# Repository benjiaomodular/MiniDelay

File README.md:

# MiniDelay

A three-knob delay module based on Rene Schmitz' PT2399 delay design. It’s a simple setup with input and output sections designed to work with Eurorack modular synthesizer levels (10Vpp).

# More info
For more information about this project, check out my website: https://benjiaomodular.com/post/2022-09-11-mini-delay/

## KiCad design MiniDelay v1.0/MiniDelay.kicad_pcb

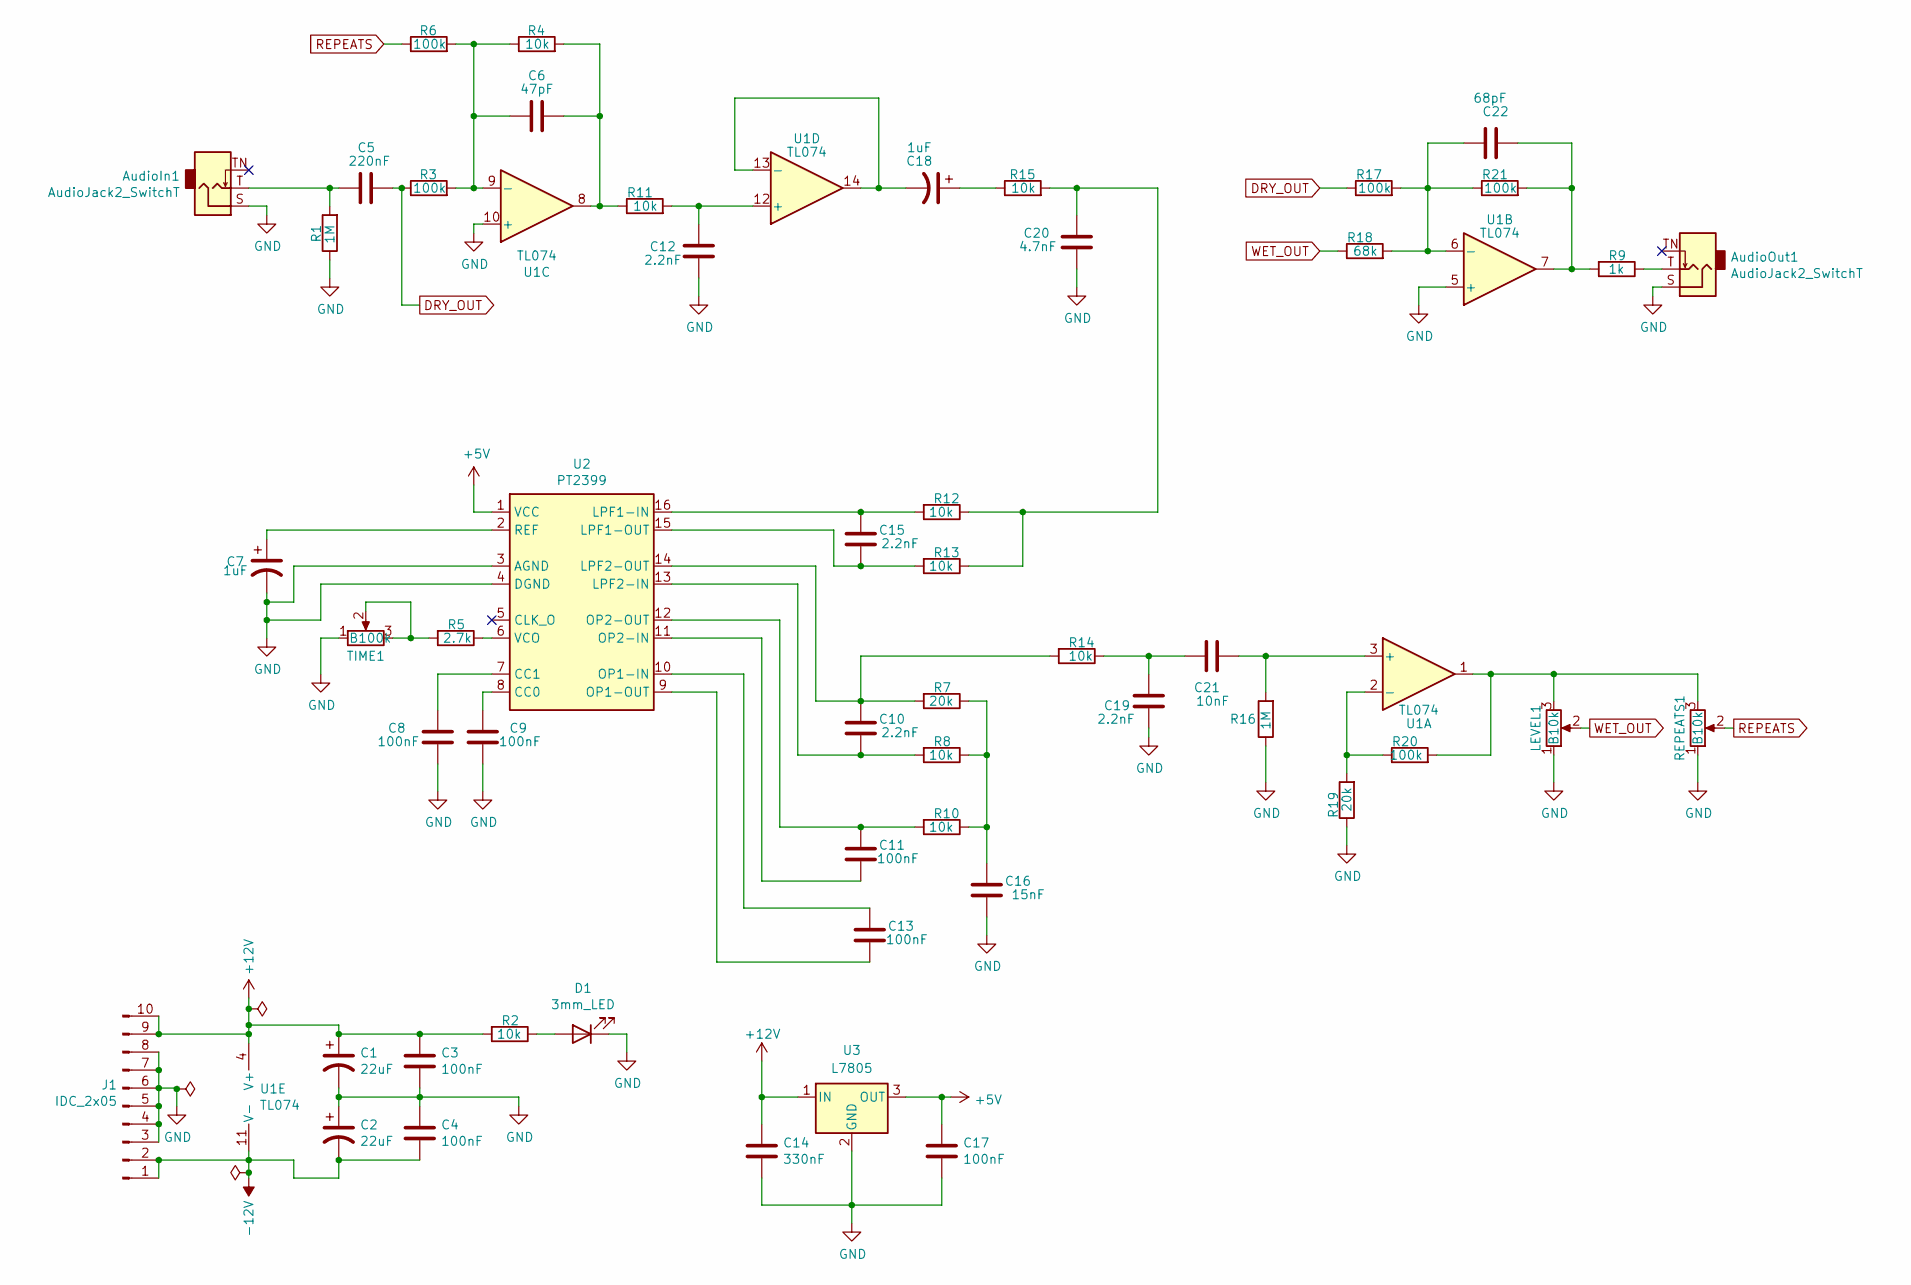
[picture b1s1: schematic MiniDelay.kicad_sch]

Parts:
AudioIn1: AudioJack2_SwitchT; AudioJack_3.5mm; Manufacturers Part Numb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 PJ-3001F
AudioOut1: AudioJack2_SwitchT; AudioJack_3.5mm; Manufacturers Part Numb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 PJ-3001F
C1, C2: 22uF; C_0805_2012Metric_Pad1.18x1.45mm_HandSolder; Mfg # CC0805KRX7R9BB104; LCSC Part # C49678
C3, C4, C8, C9, C11, C13, C17: 100nF; C_0603_1608Metric_Pad1.08x0.95mm_HandSolder; Mfg # CC0603JRX7R9BB104; LCSC Part # C91183
C5: 220nF; C_0603_1608Metric_Pad1.08x0.95mm_HandSolder; Mfg # GCM188R71H224KA64D; LCSC Part # C97857
C6: 47pF; C_0603_1608Metric_Pad1.08x0.95mm_HandSolder; Mfg # CC0603JRNPO9BN470; LCSC Part # C105622
C7, C18: 1uF; C_0603_1608Metric_Pad1.08x0.95mm_HandSolder; Mfg # UMK107AB7105KA-T; LCSC Part # C105174
C10, C12, C15, C19: 2.2nF; C_0603_1608Metric_Pad1.08x0.95mm_HandSolder; Mfg # CC0603JRNPO9BN222; LCSC Part # C107043
C14: 330nF; C_0603_1608Metric_Pad1.08x0.95mm_HandSolder; Mfg # CC0603KRX7R8BB334; LCSC Part # C107070
C16: 15nF; C_0603_1608Metric_Pad1.08x0.95mm_HandSolder; Mfg # AC0603KRX7R0BB153; LCSC Part # C2210963
C20: 4.7nF; C_0603_1608Metric_Pad1.08x0.95mm_HandSolder; Mfg # CC0603JRX7R9BB472; LCSC Part # C115060
C21: 10nF; C_0603_1608Metric_Pad1.08x0.95mm_HandSolder; Mfg # CC0603JRX7R9BB103; LCSC Part # C115056
C22: 68pF; C_0603_1608Metric_Pad1.08x0.95mm_HandSolder; Mfg # CC0603GRNPO9BN680; LCSC Part # C519457
D1: 3mm_LED; LED_D3.0mm; Manufacturers Part Numb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 EL304RD; LCSC Part # C2856645
J1: IDC_2x05; IDC-Header_2x05_P2.54mm_Vertical; Manufacturers Part Numb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 X9555WV-2X05-6TV01; LCSC Part # C706914
LEVEL1: B10k; Potentiometer_RV09; Manufacturers Part Numb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 RD901F-40-15R1-B10K
R1, R16: 1M; R_0603_1608Metric_Pad0.98x0.95mm_HandSolder; Mfg # RC0603FR-071ML; LCSC Part # C105578
R2, R4, R8, R10, R11, R12, R13, R14, R15: 10k; R_0603_1608Metric_Pad0.98x0.95mm_HandSolder; Mfg # AC0603FR-0710KL; LCSC Part # C116677
R3, R6, R17, R20, R21: 100k; R_0603_1608Metric_Pad0.98x0.95mm_HandSolder; Mfg # RC0603FR-07100KL; LCSC Part # C14675
R5: 2.7k; R_0603_1608Metric_Pad0.98x0.95mm_HandSolder; Mfg # RC0603FR-072K7L; LCSC Part # C114612
R7, R19: 20k; R_0603_1608Metric_Pad0.98x0.95mm_HandSolder; Mfg # RC0603FR-0720KL; LCSC Part # C105575
R9: 1k; R_0603_1608Metric_Pad0.98x0.95mm_HandSolder; Mfg # RC0603FR-071KL; LCSC Part # C22548
R18: 68k; R_0603_1608Metric_Pad0.98x0.95mm_HandSolder; Mfg # RC0603FR-0768KL; LCSC Part # C114633
REPEATS1: B10k; Potentiometer_RV09; Manufacturers Part Numb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 RD901F-40-15R1-B10K
TIME1: B100k; Potentiometer_RV09; Manufacturers Part Numb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 RD901F-40-15R1-B100K
U1: TL074; SOIC-14_3.9x8.7mm_P1.27mm; Mfg # TL074IDT; LCSC Part # C107644
U2: PT2399; SOP-16_4.55x10.3mm_P1.27mm; Mfg # PT2399-SN; LCSC Part # C126407
U3: L7805; TO-252-2; Mfg # L7805CDT-TR; LCSC Part # C310413

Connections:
+5V: C17.1, U2.1 (VCC), U3.3 (OUT)
+12V: C1.1, C3.1, C14.1, J1.9, J1.10, R2.2, U1.4 (V+), U3.1 (IN)
-12V: C2.2, C4.2, J1.1, J1.2, U1.11 (V-)
DRY_OUT: C5.1, R3.1, R17.1
GND: AudioIn1.S, AudioOut1.S, C1.2, C2.1, C3.2, C4.1, C7.2, C8.1, C9.1, C12.1, C14.2, C16.1, C17.2, C19.1, C20.2, D1.1 (K), J1.3, J1.4, J1.5, J1.6, J1.7, J1.8, LEVEL1.1, R1.1, R16.1, R19.1, REPEATS1.1, TIME1.1, U1.5 (+), U1.10 (+), U2.3 (AGND), U2.4 (DGND), U3.2 (GND)
unnamed: AudioIn1.T, C5.2, R1.2
unnamed: AudioOut1.T, R9.1
unnamed: C6.1, R4.2, R11.1, U1.8
unnamed: C6.2, R3.2, R4.1, R6.2, U1.9 (-)
unnamed: C7.1, U2.2 (REF)
unnamed: C8.2, U2.7 (CC1)
unnamed: C9.2, U2.8 (CC0)
unnamed: C10.1, R8.2, U2.13 (LPF2-IN)
unnamed: C10.2, R7.2, R14.2, U2.14 (LPF2-OUT)
unnamed: C11.1, U2.11 (OP2-IN)
unnamed: C11.2, R10.2, U2.12 (OP2-OUT)
unnamed: C12.2, R11.2, U1.12 (+)
unnamed: C13.1, U2.9 (OP1-OUT)
unnamed: C13.2, U2.10 (OP1-IN)
unnamed: C15.1, R13.2, U2.15 (LPF1-OUT)
unnamed: C15.2, R12.2, U2.16 (LPF1-IN)
unnamed: C16.2, R7.1, R8.1, R10.1
unnamed: C18.1, R15.1
unnamed: C18.2, U1.13 (-), U1.14
unnamed: C19.2, C21.1, R14.1
unnamed: C20.1, R12.1, R13.1, R15.2
unnamed: C21.2, R16.2, U1.3 (+)
unnamed: C22.1, R9.2, R21.2, U1.7
unnamed: C22.2, R17.2, R18.2, R21.1, U1.6 (-)
unnamed: D1.2 (A), R2.1
unnamed: LEVEL1.3, R20.2, REPEATS1.3, U1.1
unnamed: R5.1, U2.6 (VCO)
unnamed: R5.2, TIME1.2, TIME1.3
unnamed: R19.2, R20.1, U1.2 (-)
REPEATS: R6.1, REPEATS1.2
WET_OUT: LEVEL1.2, R18.1

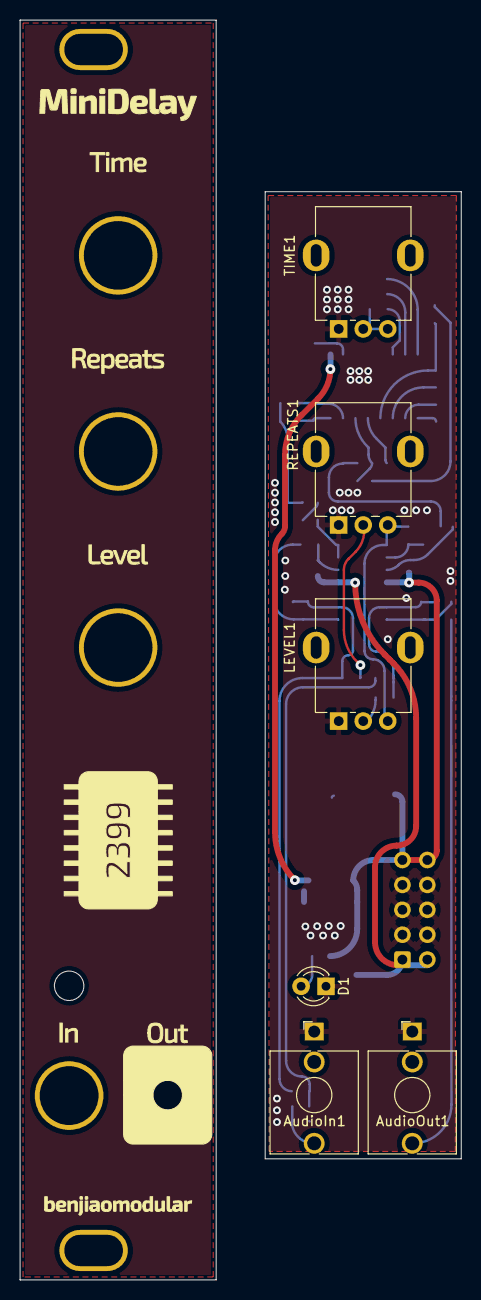
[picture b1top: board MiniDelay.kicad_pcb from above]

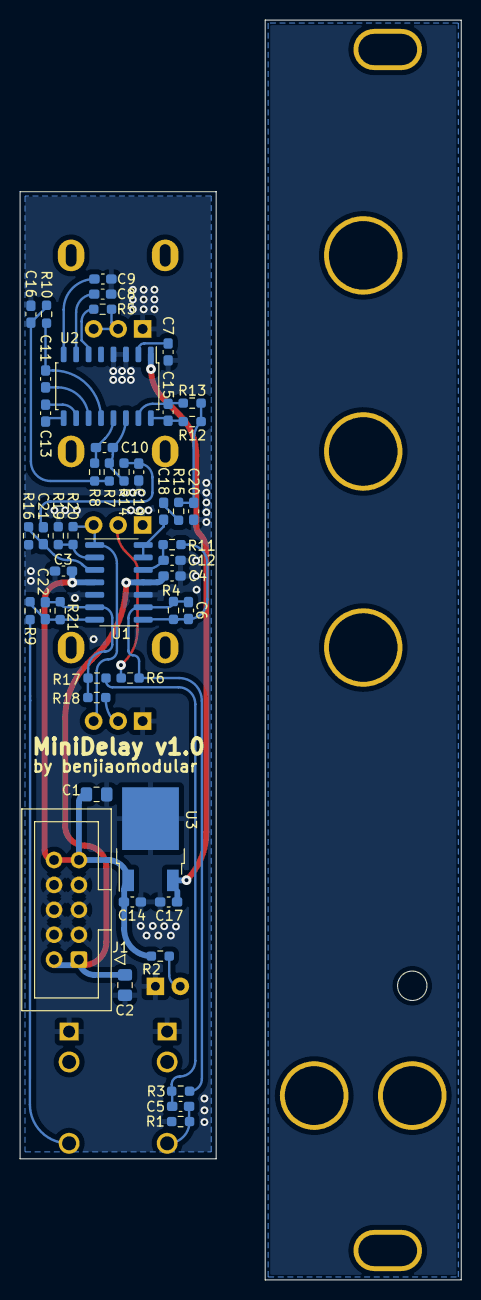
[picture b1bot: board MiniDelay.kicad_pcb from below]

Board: 2 copper layers, 20.0 x 98.7 mm, 53 parts (47 on the bottom side), 36 nets.

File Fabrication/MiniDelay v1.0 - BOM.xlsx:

Part No. | Reference | Quantity | Value | Manufacturers Name | Manufacturers Part Number | Mfg # | Part Description | Type | LCSC Part # | Package
1 | AudioIn1 AudioOut1 | 2 | AudioJack2_SwitchT | Tayda Electronics | PJ-3001F | PJ-3001F | PJ-3001F 3.5mm Mono Phone Jack | Thru-hole | - | -
2 | C1 C2 | 2 | 22uF | YAGEO | CC0805KRX7R9BB104 | CC0805KRX7R9BB104 | Multilayer Ceramic Capacitors MLCC - SMD/SMT 50 V 0.1uF X7R 0805 10% | Surface mount | C49678 | 805
3 | C10 C12 C15 C19 | 4 | 2.2nF | YAGEO | CC0603JRNPO9BN222 | CC0603JRNPO9BN222 | Multilayer Ceramic Capacitors MLCC - SMD/SMT 50V 2200pF C0G 0603 5% | Surface mount | C107043 | 603
4 | C14 | 1 | 330nF | YAGEO | CC0603KRX7R8BB334 | CC0603KRX7R8BB334 | Multilayer Ceramic Capacitors MLCC - SMD/SMT 25V 0.33uF X7R 0603 10% | Surface mount | C107070 | 603
5 | C16 | 1 | 15nF | YAGEO | AC0603KRX7R0BB153 | AC0603KRX7R0BB153 | Multilayer Ceramic Capacitors MLCC - SMD/SMT 100 V 0.015 uF X7R 0603 10% AEC-Q2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 | Surface mount | C2210963 | 603
6 | C20 | 1 | 4.7nF | YAGEO | CC0603JRX7R9BB472 | CC0603JRX7R9BB472 | Multilayer Ceramic Capacitors MLCC - SMD/SMT 50V 4700pF X7R 0603 5% | Surface mount | C115060 | 603
7 | C21 | 1 | 10nF | YAGEO | CC0603JRX7R9BB103 | CC0603JRX7R9BB103 | Multilayer Ceramic Capacitors MLCC - SMD/SMT 50V 0.01uF X7R 0603 5% | Surface mount | C115056 | 603
8 | C22 | 1 | 68pF | YAGEO | CC0603GRNPO9BN680 | CC0603GRNPO9BN680 | Multilayer Ceramic Capacitors MLCC - SMD/SMT 50 V 68 pF C0G 0603 2% | Surface mount | C519457 | 603
9 | C3 C4 C8 C9 C11 C13 C17 | 7 | 100nF | YAGEO | CC0603JRX7R9BB104 | CC0603JRX7R9BB104 | Multilayer Ceramic Capacitors MLCC - SMD/SMT 50 V 0.1uF X7R 0603 5% | Surface mount | C91183 | 603
10 | C5 | 1 | 220nF | Murata Electronics | GCM188R71H224KA64D | GCM188R71H224KA64D | Multilayer Ceramic Capacitors MLCC - SMD/SMT .22UF 50V 10% 0603 | Surface mount | C97857 | 603
11 | C6 | 1 | 47pF | YAGEO | CC0603JRNPO9BN470 | CC0603JRNPO9BN470 | Multilayer Ceramic Capacitors MLCC - SMD/SMT 50 V 47 pF C0G 0603 5% | Surface mount | C105622 | 603
12 | C7 C18 | 2 | 1uF | Taiyo Yuden | UMK107AB7105KA-T | UMK107AB7105KA-T | Multilayer Ceramic Capacitors MLCC - SMD/SMT 0603 50VDC 1uF 10% X7R | Surface mount | C105174 | 603
13 | D1 | 1 | 3mm_LED | EKINGLUX | EL304RD | EL304RD | 3.0mm Round Through Hole LED | Thru-hole | C2856645 | -
14 | J1 | 1 | IDC_2x05 | XKB Connectivity | X9555WV-2X05-6TV01 | X9555WV-2X05-6TV01 | IDC Connector 2x05 2.54mm Pitch Straight | Thru-hole | C706914 | -
15 | LEVEL1 REPEATS1 | 2 | B10k | Alpha (Taiwan) | RD901F-40-15R1-B10K | RD901F-40-15R1-B10K | 10K OHM Linear Taper Potentiometer Round Shaft PCB 9mm | Thru-hole | - | RD901F
16 | R1 R16 | 2 | 1M | YAGEO | RC0603FR-071ML | RC0603FR-071ML | Thick Film Resistors - SMD 1 MOhms 100mW 0603 1% | Surface mount | C105578 | 603
17 | R18 | 1 | 68k | YAGEO | RC0603FR-0768KL | RC0603FR-0768KL | Thick Film Resistors - SMD 68 kOhms 100mW 0603 1% | Surface mount | C114633 | 603
18 | R2 R4 R8 R10 R11 R12 R13 R14 R15 | 9 | 10k | YAGEO | AC0603FR-0710KL | AC0603FR-0710KL | Thick Film Resistors - SMD 10 kOhms 100mW 0603 1% AEC-Q200 | Surface mount | C116677 | 603
19 | R3 R6 R17 R20 R21 | 5 | 100k | YAGEO | RC0603FR-07100KL | RC0603FR-07100KL | Thick Film Resistors - SMD 100 kOhms 100mW 0603 1% | Surface mount | C14675 | 603
20 | R5 | 1 | 2.7k | YAGEO | RC0603FR-072K7L | RC0603FR-072K7L | Thick Film Resistors - SMD 2.7 kOhms 100mW 0603 1% | Surface mount | C114612 | 603
21 | R7 R19 | 2 | 20k | YAGEO | RC0603FR-0720KL | RC0603FR-0720KL | Thick Film Resistors - SMD 20 kOhms 100mW 0603 1% | Surface mount | C105575 | 603
22 | R9 | 1 | 1k | YAGEO | RC0603FR-071KL | RC0603FR-071KL | Thick Film Resistors - SMD 1 kOhms 100mW 0603 1% | Surface mount | C22548 | 603
23 | TIME1 | 1 | B100k | Alpha (Taiwan) | RD901F-40-15R1-B100K | RD901F-40-15R1-B100K | 100K OHM Linear Taper Potentiometer Round Shaft PCB 9mm | Thru-hole | - | RD901F
24 | U1 | 1 | TL074 | STMicroelectronics | TL074IDT | TL074IDT | Operational Amplifiers - Op Amps Quad Low Noise JFET | Surface mount | C107644 | SOIC-14_150mil
25 | U2 | 1 | PT2399 | PTC(Princeton Tech) | PT2399-SN | PT2399-SN | SOP-16_150mil Audio Interface ICs ROHS | Surface mount | C126407 | SOP-16_150mil
26 | U3 | 1 | L7805 | STMicroelectronics | L7805CDT-TR | L7805CDT-TR | 62dB@(120Hz) 1.5A 2V@(1A) Fixed 5V~5V Positive 1 35V TO-252-3 Linear Voltage Re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 | Surface mount | C310413 | TO-252-3
 |  | 53

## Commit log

2022-10-11 Hello git
2022-10-24 Moved everything to SMD
2022-10-24 Updated bom using LCSC
2022-10-25 Worked on BOM
2022-10-25 Complete BOM
2022-10-25 Added part descriptions
2022-11-14 Final v1.0 PCB
2022-11-14 initialzied README
2022-11-15 Refactored BOM
2022-11-15 Cleanup files
2022-11-15 More cleanup
2022-11-15 Added updated readme
2022-11-18 Removed outdated bom
2023-06-27 Minor updates to kicad files
2023-06-27 Added license file
2024-11-09 Cleaned up fabrication files
